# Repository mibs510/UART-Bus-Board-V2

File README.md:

# UART Bus Board V2
  A UART bus to configure MKS SERVO42C closed looped stepper drivers on my 5' x 6.5' laser CNC

# Block Diagram

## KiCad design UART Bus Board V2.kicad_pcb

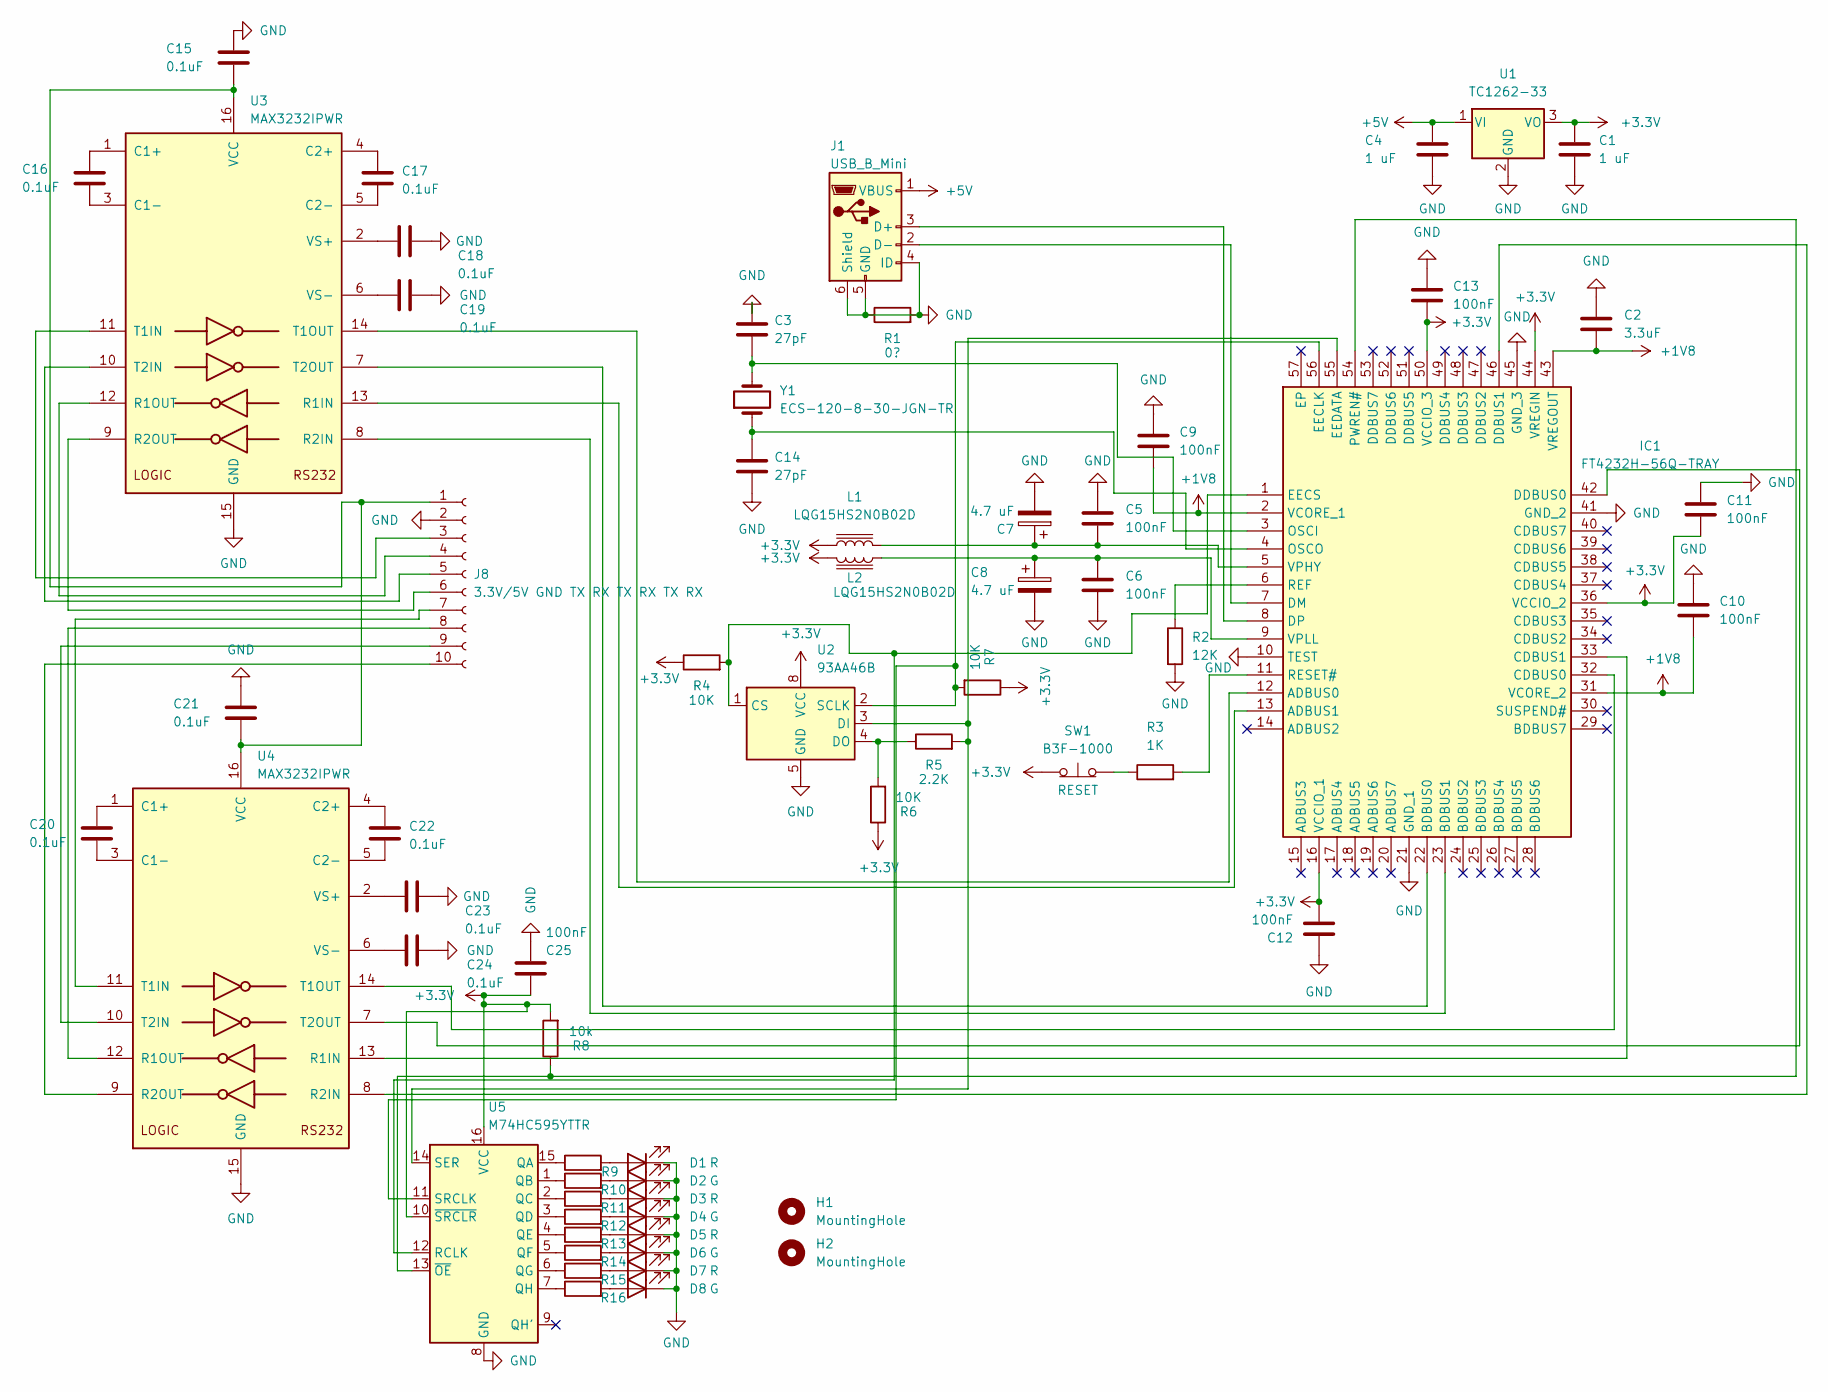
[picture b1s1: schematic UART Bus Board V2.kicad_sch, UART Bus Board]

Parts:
C1, C4: 1 uF; C_0201_0603Metric
C2: 3.3uF; C_0201_0603Metric
C3, C14: 27pF; C_0201_0603Metric
C5, C6, C9, C10, C11, C12, C13, C25: 100nF; C_0201_0603Metric
C7, C8: 4.7 uF; C_0201_0603Metric
C15, C16, C17, C18, C19, C20, C21, C22, C23, C24: 0.1uF; C_0201_0603Metric
D1, D3, D5, D7: R; LED_0603_1608Metric
D2, D4, D6, D8: G; LED_0603_1608Metric
H1, H2: MountingHole; MountingHole_2.2mm_M2
IC1: FT4232H-56Q-TRAY; QFN-56-1EP_8x8mm_P0.5mm_EP5.9x5.9mm; Mouser Part Number 895-FT4232H-56Q-TRAY
J1: USB_B_Mini; USB_Mini-B_Tensility_54-00023_Vertical
J8: 3.3V/5V GND TX RX TX RX TX RX; JST_XH_B10B-XH-A_1x10_P2.50mm_Vertical
L1, L2: LQG15HS2N0B02D; L_0402_1005Metric
R1: 0?; R_0201_0603Metric
R2: 12K; R_0201_0603Metric
R3: 1K; R_0201_0603Metric
R4, R6, R7: 10K; R_0201_0603Metric
R5: 2.2K; R_0201_0603Metric
R8: 10k; R_0201_0603Metric
R9, R10, R11, R12, R13, R14, R15, R16: 330R; R_0201_0603Metric
SW1: B3F-1000; SW_PUSH_6mm
U1: TC1262-33; SOT-223-3_TabPin2
U2: 93AA46B; MSOP-8_3x3mm_P0.65mm
U3, U4: MAX3232IPWR; TSSOP-16_4.4x5mm_P0.65mm
U5: M74HC595YTTR; TSSOP-16_4.4x5mm_P0.65mm
Y1: ECS-120-8-30-JGN-TR; Crystal_SMD_5032-2Pin_5.0x3.2mm

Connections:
+3.3V: C1.1, C11.2, C12.2, C13.2, C25.2, IC1.16 (VCCIO_1), IC1.36 (VCCIO_2), IC1.44 (VREGIN), IC1.50 (VCCIO_3), L1.1, L2.2, R4.1, R6.1, R7.1, R8.2, SW1.1 (A), U1.3 (VO), U2.8 (VCC), U5.10 (~SRCLR), U5.16 (VCC)
+5V: C4.1, J1.1 (VBUS), U1.1 (VI)
GND: C1.2, C2.1, C3.1, C4.2, C5.1, C6.2, C7.2, C8.2, C9.1, C10.1, C11.1, C12.1, C13.1, C14.2, C15.1, C18.1, C19.1, C21.1, C23.1, C24.1, C25.1, D1.1 (K), D2.1 (K), D3.1 (K), D4.1 (K), D5.1 (K), D6.1 (K), D7.1 (K), D8.1 (K), IC1.10 (TEST), IC1.21 (GND_1), IC1.41 (GND_2), IC1.45 (GND_3), J1.4 (ID), J1.5 (GND), J1.6 (Shield), J8.2, R1.1, R1.2, R2.2, U1.2 (GND), U2.5 (GND), U3.15 (GND), U4.15 (GND), U5.8 (GND)
unnamed: D1.2 (A), R9.2
unnamed: D2.2 (A), R10.2
unnamed: D3.2 (A), R11.2
unnamed: D4.2 (A), R12.2
unnamed: D5.2 (A), R13.2
unnamed: D6.2 (A), R14.2
unnamed: D7.2 (A), R15.2
unnamed: D8.2 (A), R16.2
unnamed: IC1.12 (ADBUS0), U3.14 (T1OUT)
unnamed: IC1.13 (ADBUS1), U3.13 (R1IN)
unnamed: IC1.22 (BDBUS0), U3.7 (T2OUT)
unnamed: IC1.23 (BDBUS1), U3.8 (R2IN)
unnamed: IC1.32 (CDBUS0), U4.14 (T1OUT)
unnamed: IC1.33 (CDBUS1), U4.13 (R1IN)
unnamed: IC1.42 (DDBUS0), U4.7 (T2OUT)
unnamed: IC1.46 (DDBUS1), U4.8 (R2IN)
unnamed: IC1.7 (DM), J1.2 (D-)
unnamed: IC1.8 (DP), J1.3 (D+)
unnamed: IC1.56 (EECLK), R7.2, U2.2 (SCLK), U5.11 (SRCLK)
unnamed: IC1.1 (EECS), R4.2, U2.1 (CS), U5.12 (RCLK)
unnamed: IC1.55 (EEDATA), R5.2, U2.3 (DI), U5.14 (SER)
unnamed: C3.2, IC1.3 (OSCI), Y1.2
unnamed: C14.1, IC1.4 (OSCO), Y1.1
unnamed: IC1.54 (PWREN#), R8.1, U5.13 (~OE)
unnamed: IC1.6 (REF), R2.1
unnamed: IC1.11 (RESET#), R3.2
unnamed: C5.2, C7.1, IC1.5 (VPHY), L1.2
unnamed: C6.1, C8.1, IC1.9 (VPLL), L2.1
unnamed: C15.2, C21.2, J8.1, U3.16 (VCC), U4.16 (VCC)
unnamed: J8.3, U3.11 (T1IN)
unnamed: J8.4, U3.12 (R1OUT)
unnamed: J8.5, U3.10 (T2IN)
unnamed: J8.6, U3.9 (R2OUT)
unnamed: J8.7, U4.11 (T1IN)
unnamed: J8.8, U4.12 (R1OUT)
unnamed: J8.9, U4.10 (T2IN)
unnamed: J8.10, U4.9 (R2OUT)
unnamed: R3.1, SW1.2 (B)
unnamed: R5.1, R6.2, U2.4 (DO)
unnamed: C16.1, U3.1 (C1+)
unnamed: C16.2, U3.3 (C1-)
unnamed: C17.1, U3.4 (C2+)
unnamed: C17.2, U3.5 (C2-)
unnamed: C18.2, U3.2 (VS+)
unnamed: C19.2, U3.6 (VS-)
unnamed: C20.1, U4.1 (C1+)
unnamed: C20.2, U4.3 (C1-)
unnamed: C22.1, U4.4 (C2+)
unnamed: C22.2, U4.5 (C2-)
unnamed: C23.2, U4.2 (VS+)
unnamed: C24.2, U4.6 (VS-)
unnamed: R9.1, U5.15 (QA)
unnamed: R10.1, U5.1 (QB)
unnamed: R11.1, U5.2 (QC)
unnamed: R12.1, U5.3 (QD)
unnamed: R13.1, U5.4 (QE)
unnamed: R14.1, U5.5 (QF)
unnamed: R15.1, U5.6 (QG)
unnamed: R16.1, U5.7 (QH)

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
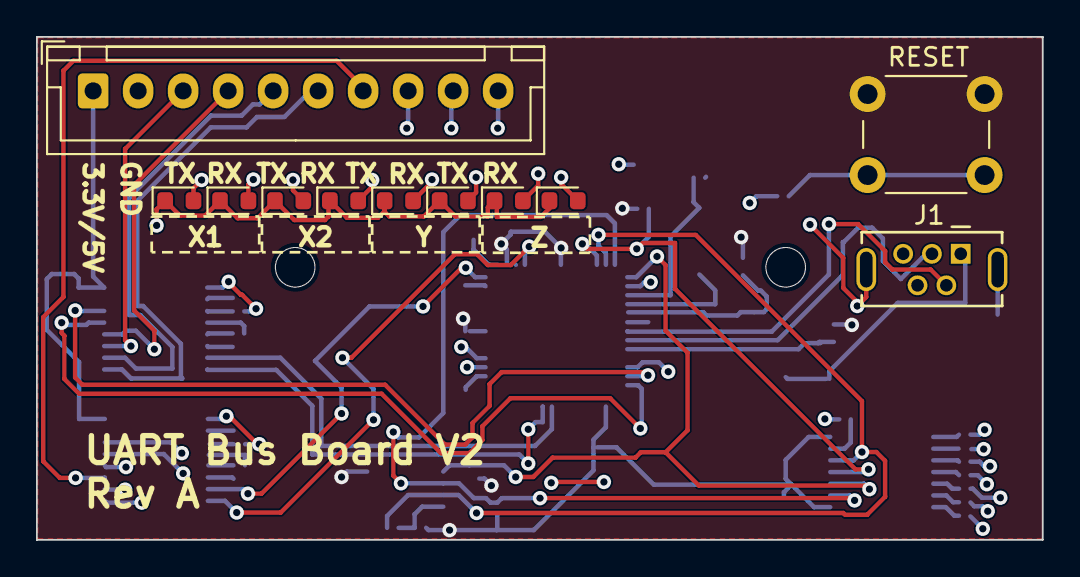
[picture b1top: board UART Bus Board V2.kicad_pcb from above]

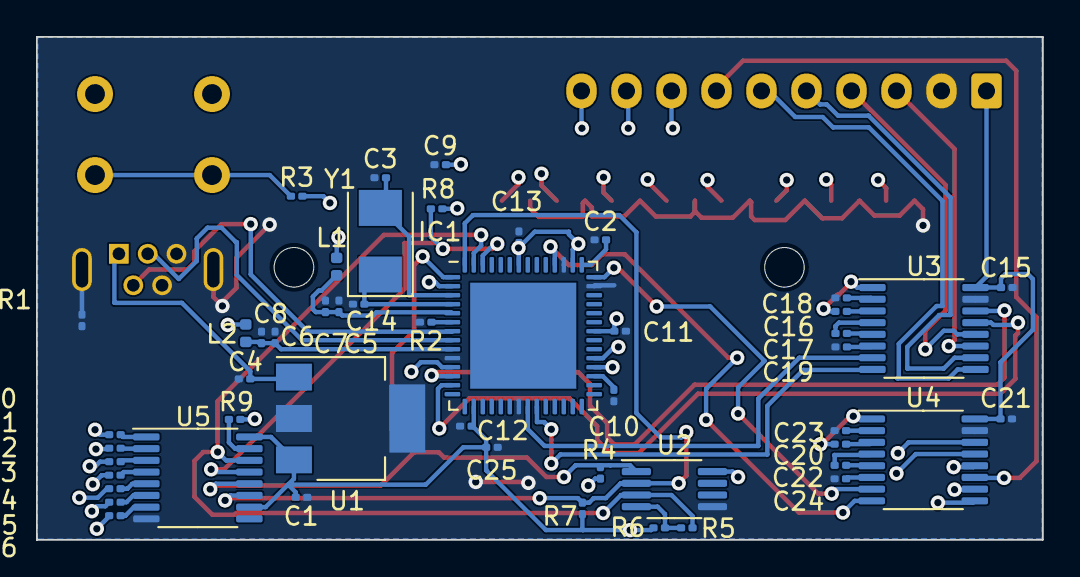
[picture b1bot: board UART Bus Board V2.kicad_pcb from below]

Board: 4 copper layers, 55.9 x 27.9 mm, 63 parts (50 on the bottom side), 65 nets.

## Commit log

2023-08-21 Initial commit. Rev A
    Initial commit! Starting with revision A!
2023-08-21 Block diagram & .gitignore
    Added block diagram and added exclusions to .gitignore
2023-08-21 Buried/Blinded Vias
    Unburied vias that didn't need to be buried in the first place.
2023-08-21 Errors & warning
    Fixed a couple of errors and warnings that the DRC reported.
2023-08-27 clearances/minimums + burried vias + PCBWay
    Lowered clearances and minimums on the top fill layer
    Removed three buried/hidden vias
    Passing on PCBWay without issues
